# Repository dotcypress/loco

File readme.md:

# loco

Toy CNC platform.

## License

Licensed under either of

- Apache License, Version 2.0 ([LICENSE-APACHE](LICENSE-APACHE) or
  http://www.apache.org/licenses/LICENSE-2.0)
- MIT license ([LICENSE-MIT](LICENSE-MIT) or http://opensource.org/licenses/MIT)

at your option.

### Contribution

Unless you explicitly state otherwise, any contribution intentionally submitted
for inclusion in the work by you, as defined in the Apache-2.0 license, shall be
dual licensed as above, without any additional terms or conditions.

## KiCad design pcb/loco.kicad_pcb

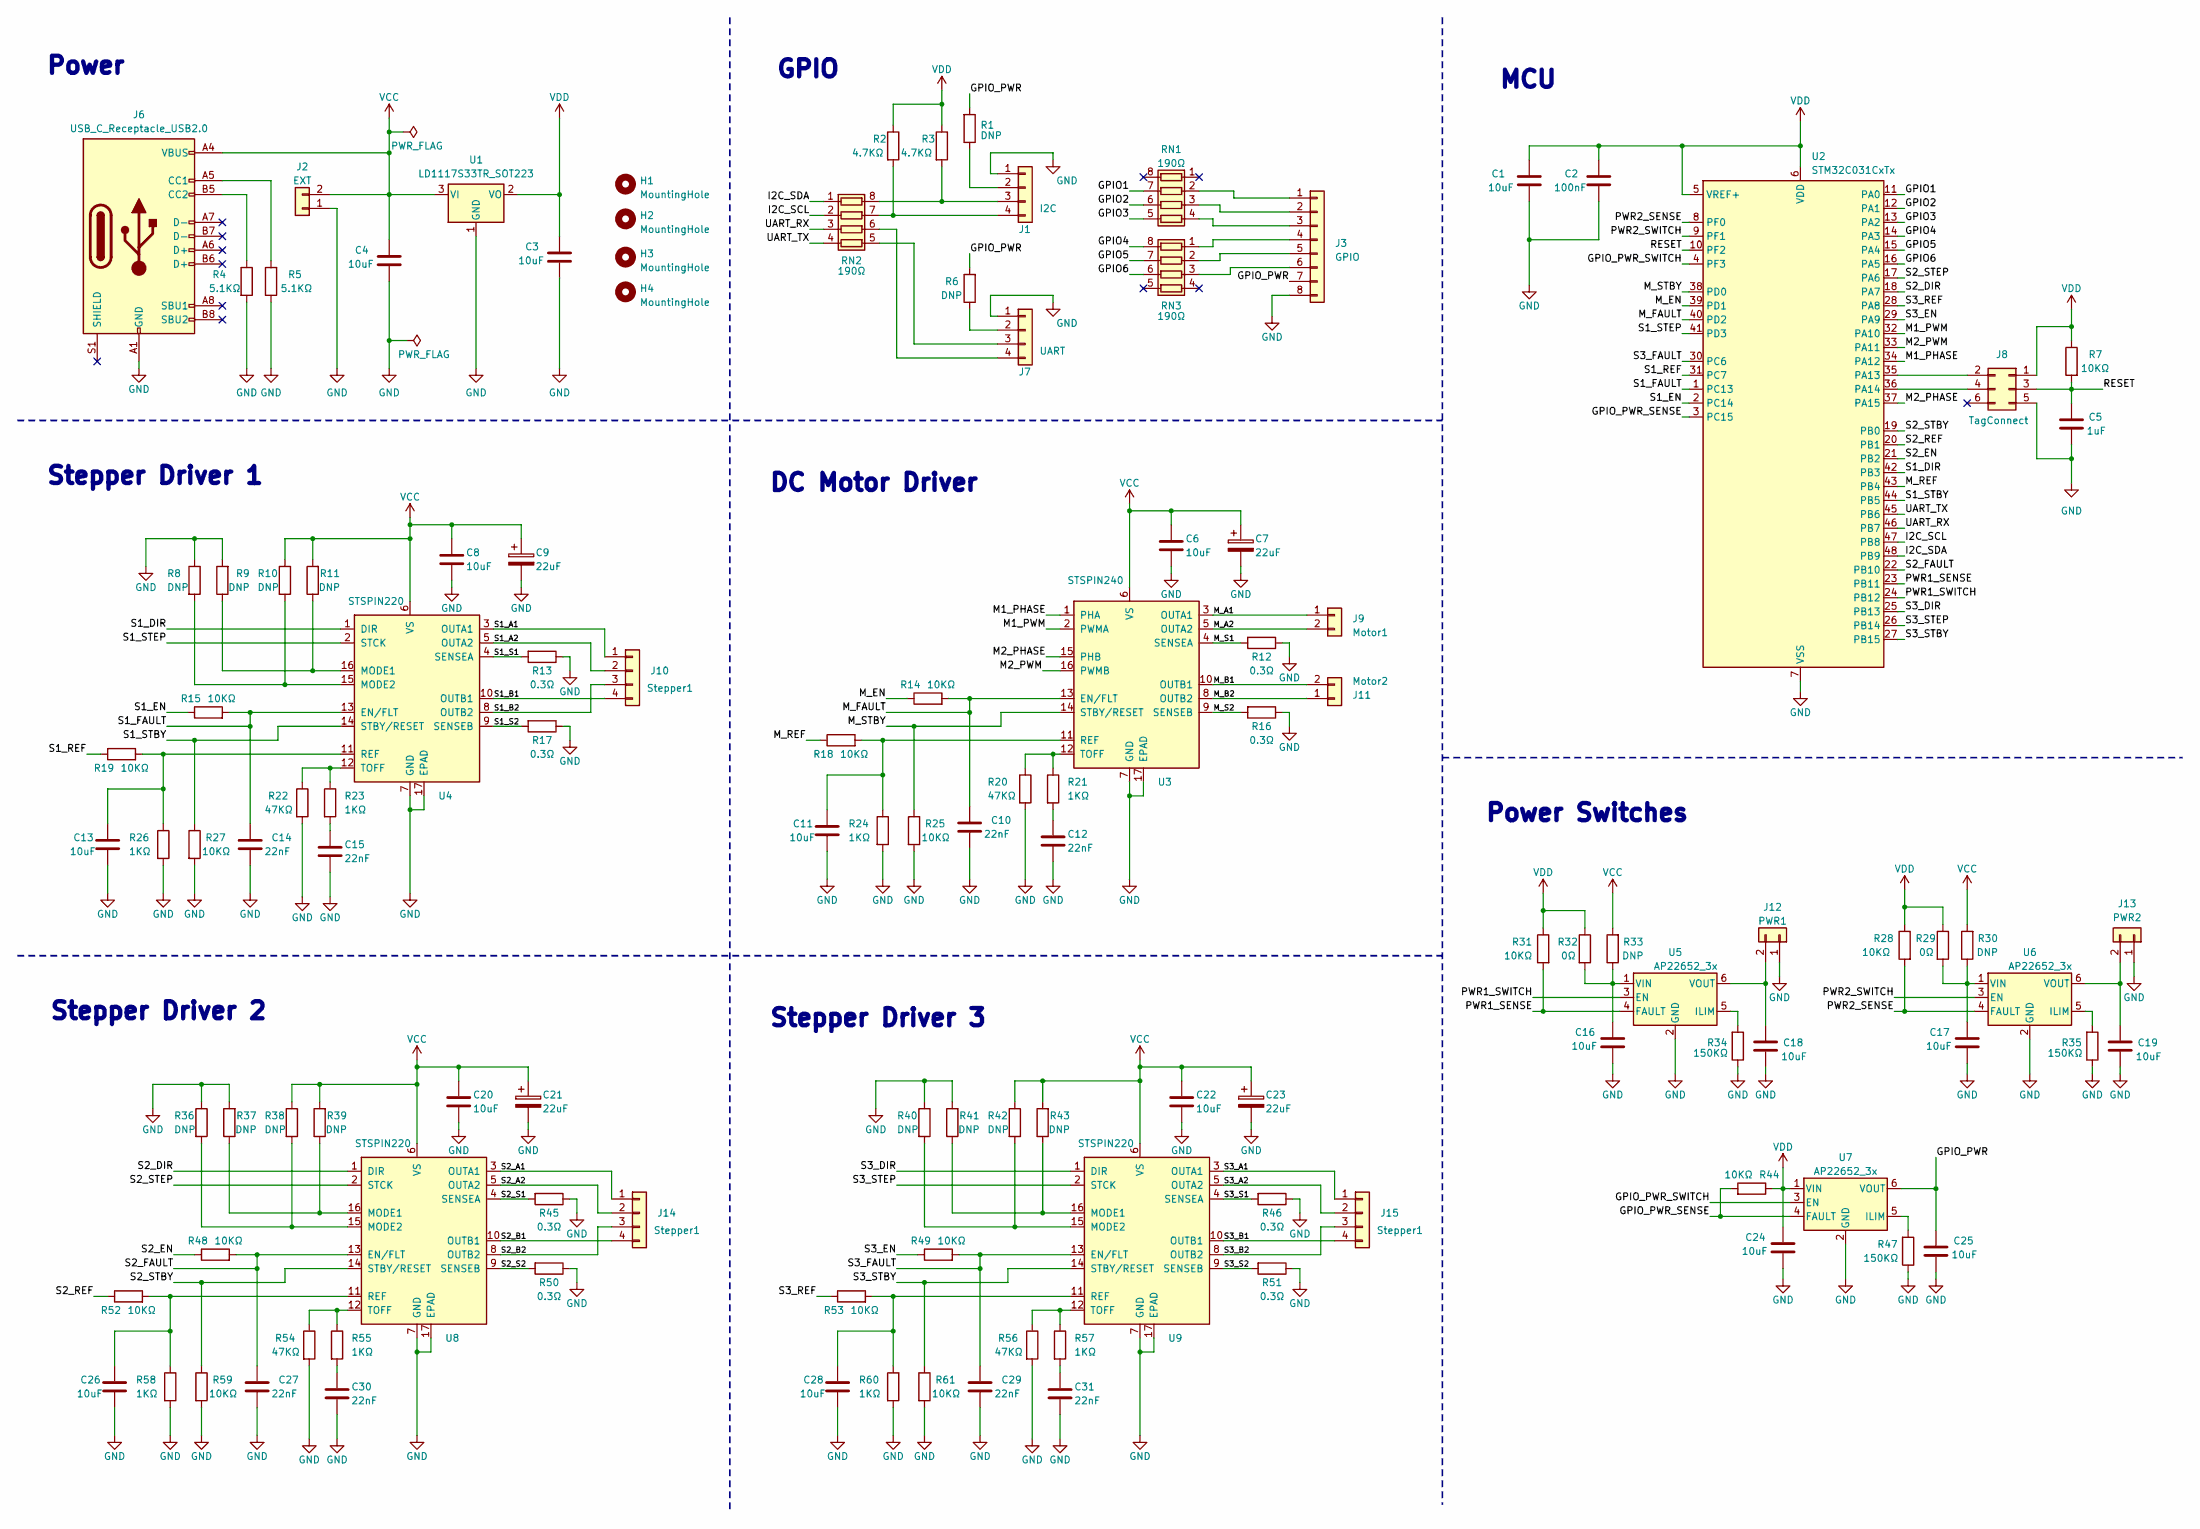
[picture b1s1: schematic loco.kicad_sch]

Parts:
C1, C3, C4, C6, C8, C11, C13, C16, C17, C18, C19, C20, C22, C24, C25, C26, C28: 10uF; C_0603_1608Metric
C2: 100nF; C_0603_1608Metric
C5: 1uF; C_0603_1608Metric
C7, C9, C21, C23: 22uF; CP_Elec_4x4.5
C10, C12, C14, C15, C27, C29, C30, C31: 22nF; C_0603_1608Metric
H1, H2, H3, H4: MountingHole; MountingHole_3.2mm_M3_Pad_Via
J1: I2C; JST_SH_BM04B-SRSS-TB_1x04-1MP_P1.00mm_Vertical
J2: EXT; JST_PH_B2B-PH-K_1x02_P2.00mm_Vertical
J3: GPIO; Header_03x06_P2.54mm_Vertical
J6: USB_C_Receptacle_USB2.0; USB_C_Receptacle_JAE_DX07S016JA3R1500
J7: UART; JST_SH_BM04B-SRSS-TB_1x04-1MP_P1.00mm_Vertical
J8: TagConnect; Tag-Connect_TC2030-IDC-NL_2x03_P1.27mm_Vertical
J9: Motor1; JST_PH_B2B-PH-K_1x02_P2.00mm_Vertical
J10, J14, J15: Stepper1; JST_PH_B4B-PH-K_1x04_P2.00mm_Vertical
J11: Motor2; JST_PH_B2B-PH-K_1x02_P2.00mm_Vertical
J12: PWR1; JST_PH_B2B-PH-K_1x02_P2.00mm_Vertical
J13: PWR2; JST_PH_B2B-PH-K_1x02_P2.00mm_Vertical
R1, R6, R8, R9, R10, R11, R30, R33, R36, R37, R38, R39, R40, R41, R42, R43: DNP; R_0603_1608Metric
R2, R3: 4.7KΩ; R_0603_1608Metric
R4, R5: 5.1KΩ; R_0603_1608Metric
R7, R14, R15, R18, R19, R25, R27, R28, R31, R44, R48, R49, R52, R53, R59, R61: 10KΩ; R_0603_1608Metric
R12, R13, R16, R17, R45, R46, R50, R51: 0.3Ω; R_1206_3216Metric
R20, R22, R54, R56: 47KΩ; R_0603_1608Metric
R21, R23, R24, R26, R55, R57, R58, R60: 1KΩ; R_0603_1608Metric
R29, R32: 0Ω; R_0603_1608Metric
R34, R35, R47: 150KΩ; R_0603_1608Metric
RN1, RN2, RN3: 190Ω; R_Array_Convex_4x0603
U1: LD1117S33TR_SOT223; SOT-223-3_TabPin2
U2: STM32C031CxTx; LQFP-48_7x7mm_P0.5mm
U3: STSPIN240; VQFN-16-1EP_3x3mm_P0.5mm_EP1.8x1.8mm
U4, U8, U9: STSPIN220; VQFN-16-1EP_3x3mm_P0.5mm_EP1.8x1.8mm
U5, U6, U7: AP22652_3x; SOT-23-6

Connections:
/GPIO1: RN1.7 (R2.2), U2.11 (PA0)
/GPIO2: RN1.6 (R3.2), U2.12 (PA1)
/GPIO3: RN1.5 (R4.2), U2.13 (PA2)
/GPIO4: RN3.8 (R1.2), U2.14 (PA3)
/GPIO5: RN3.7 (R2.2), U2.15 (PA4)
/GPIO6: RN3.6 (R3.2), U2.16 (PA5)
/GPIO_PWR: C25.1, J3.7, R1.2, R6.2, U7.6 (VOUT)
/GPIO_PWR_SENSE: R44.2, U2.3 (PC15), U7.4 (FAULT)
/GPIO_PWR_SWITCH: U2.4 (PF3), U7.3 (EN)
/I2C_SCL: RN2.2 (R2.1), U2.47 (PB8)
/I2C_SDA: RN2.1 (R1.1), U2.48 (PB9)
/M1_PHASE: U2.34 (PA12), U3.1 (PHA)
/M1_PWM: U2.32 (PA10), U3.2 (PWMA)
/M2_PHASE: U2.37 (PA15), U3.15 (PHB)
/M2_PWM: U2.33 (PA11), U3.16 (PWMB)
/M_A1: J9.1, U3.3 (OUTA1)
/M_A2: J9.2, U3.5 (OUTA2)
/M_B1: J11.2, U3.10 (OUTB1)
/M_B2: J11.1, U3.8 (OUTB2)
/M_EN: R14.1, U2.39 (PD1)
/M_FAULT: C10.1, R14.2, U2.40 (PD2), U3.13 (EN/FLT)
/M_REF: R18.1, U2.43 (PB4)
/M_S1: R12.2, U3.4 (SENSEA)
/M_S2: R16.2, U3.9 (SENSEB)
/M_STBY: R25.1, U2.38 (PD0), U3.14 (STBY/RESET)
/PWR1_SENSE: R31.2, U2.23 (PB11), U5.4 (FAULT)
/PWR1_SWITCH: U2.24 (PB12), U5.3 (EN)
/PWR2_SENSE: R28.2, U2.8 (PF0), U6.4 (FAULT)
/PWR2_SWITCH: U2.9 (PF1), U6.3 (EN)
/RESET: C5.1, J8.3, R7.2, U2.10 (PF2)
/S1_A1: J10.1, U4.3 (OUTA1)
/S1_A2: J10.2, U4.5 (OUTA2)
/S1_B1: J10.4, U4.10 (OUTB1)
/S1_B2: J10.3, U4.8 (OUTB2)
/S1_DIR: U2.42 (PB3), U4.1 (DIR)
/S1_EN: R15.1, U2.2 (PC14)
/S1_FAULT: C14.1, R15.2, U2.1 (PC13), U4.13 (EN/FLT)
/S1_REF: R19.1, U2.31 (PC7)
/S1_S1: R13.2, U4.4 (SENSEA)
/S1_S2: R17.2, U4.9 (SENSEB)
/S1_STBY: R27.1, U2.44 (PB5), U4.14 (STBY/RESET)
/S1_STEP: U2.41 (PD3), U4.2 (STCK)
/S2_A1: J14.1, U8.3 (OUTA1)
/S2_A2: J14.2, U8.5 (OUTA2)
/S2_B1: J14.4, U8.10 (OUTB1)
/S2_B2: J14.3, U8.8 (OUTB2)
/S2_DIR: U2.18 (PA7), U8.1 (DIR)
/S2_EN: R48.1, U2.21 (PB2)
/S2_FAULT: C27.1, R48.2, U2.22 (PB10), U8.13 (EN/FLT)
/S2_REF: R52.1, U2.20 (PB1)
/S2_S1: R45.2, U8.4 (SENSEA)
/S2_S2: R50.2, U8.9 (SENSEB)
/S2_STBY: R59.1, U2.19 (PB0), U8.14 (STBY/RESET)
/S2_STEP: U2.17 (PA6), U8.2 (STCK)
/S3_A1: J15.1, U9.3 (OUTA1)
/S3_A2: J15.2, U9.5 (OUTA2)
/S3_B1: J15.4, U9.10 (OUTB1)
/S3_B2: J15.3, U9.8 (OUTB2)
/S3_DIR: U2.25 (PB13), U9.1 (DIR)
/S3_EN: R49.1, U2.29 (PA9)
/S3_FAULT: C29.1, R49.2, U2.30 (PC6), U9.13 (EN/FLT)
/S3_REF: R53.1, U2.28 (PA8)
/S3_S1: R46.2, U9.4 (SENSEA)
/S3_S2: R51.2, U9.9 (SENSEB)
/S3_STBY: R61.1, U2.27 (PB15), U9.14 (STBY/RESET)
/S3_STEP: U2.26 (PB14), U9.2 (STCK)
/UART_RX: RN2.3 (R3.1), U2.46 (PB7)
/UART_TX: RN2.4 (R4.1), U2.45 (PB6)
GND: C1.2, C2.2, C3.2, C4.2, C5.2, C6.2, C7.2, C8.2, C9.2, C10.2, C11.2, C12.2, C13.2, C14.2, C15.2, C16.2, C17.2, C18.2, C19.2, C20.2, C21.2, C22.2, C23.2, C24.2, C25.2, C26.2, C27.2, C28.2, C29.2, C30.2, C31.2, J1.1, J2.1, J3.8, J6.A1 (GND), J7.1, J8.5, J12.1, J13.1, R4.2, R5.1, R8.1, R9.2, R12.1, R13.1, R16.1, R17.1, R20.2, R22.2, R24.2, R25.2, R26.2, R27.2, R34.1, R35.1, R36.1, R37.2, R40.1, R41.2, R45.1, R46.1, R47.1, R50.1, R51.1, R54.2, R56.2, R58.2, R59.2, R60.2, R61.2, U1.1 (GND), U2.7 (VSS), U3.7 (GND), U3.17 (EPAD), U4.7 (GND), U4.17 (EPAD), U5.2 (GND), U6.2 (GND), U7.2 (GND), U8.7 (GND), U8.17 (EPAD), U9.7 (GND), U9.17 (EPAD)
unnamed: C12.1, R21.2
unnamed: C15.1, R23.2
unnamed: C30.1, R55.2
unnamed: C31.1, R57.2
unnamed: J1.2, R1.1
unnamed: J1.3, R3.2, RN2.8 (R1.2)
unnamed: J1.4, R2.2, RN2.7 (R2.2)
unnamed: J3.1, RN1.2 (R2.1)
unnamed: J3.2, RN1.3 (R3.1)
unnamed: J3.3, RN1.4 (R4.1)
unnamed: J3.4, RN3.1 (R1.1)
unnamed: J3.5, RN3.2 (R2.1)
unnamed: J3.6, RN3.3 (R3.1)
unnamed: J6.A5 (CC1), R5.2
unnamed: J6.B5 (CC2), R4.1
unnamed: J7.2, R6.1
unnamed: J7.3, RN2.5 (R4.2)
unnamed: J7.4, RN2.6 (R3.2)
unnamed: J8.2, U2.35 (PA13)
unnamed: J8.4, U2.36 (PA14)
unnamed: C18.1, J12.2, U5.6 (VOUT)
unnamed: C19.1, J13.2, U6.6 (VOUT)
unnamed: C11.1, R18.2, R24.1, U3.11 (REF)
unnamed: R20.1, R21.1, U3.12 (TOFF)
unnamed: R9.1, R11.1, U4.16 (MODE1)
unnamed: R8.2, R10.2, U4.15 (MODE2)
unnamed: C13.1, R19.2, R26.1, U4.11 (REF)
unnamed: R22.1, R23.1, U4.12 (TOFF)
unnamed: R34.2, U5.5 (ILIM)
unnamed: C16.1, R32.2, R33.1, U5.1 (VIN)
unnamed: R35.2, U6.5 (ILIM)
unnamed: C17.1, R29.2, R30.1, U6.1 (VIN)
unnamed: R47.2, U7.5 (ILIM)
unnamed: R37.1, R39.1, U8.16 (MODE1)
unnamed: R36.2, R38.2, U8.15 (MODE2)
unnamed: C26.1, R52.2, R58.1, U8.11 (REF)
unnamed: R54.1, R55.1, U8.12 (TOFF)
unnamed: R41.1, R43.1, U9.16 (MODE1)
unnamed: R40.2, R42.2, U9.15 (MODE2)
unnamed: C28.1, R53.2, R60.1, U9.11 (REF)
unnamed: R56.1, R57.1, U9.12 (TOFF)
VCC: C4.1, C6.1, C7.1, C8.1, C9.1, C20.1, C21.1, C22.1, C23.1, J2.2, J6.A4 (VBUS), J6.A9 (VBUS), R10.1, R11.2, R30.2, R33.2, R38.1, R39.2, R42.1, R43.2, U1.3 (VI), U3.6 (VS), U4.6 (VS), U8.6 (VS), U9.6 (VS)
VDD: C1.1, C2.1, C3.1, C24.1, J8.1, R2.1, R3.1, R7.1, R28.1, R29.1, R31.1, R32.1, R44.1, U1.2 (VO), U2.5 (VREF+), U2.6 (VDD), U7.1 (VIN)

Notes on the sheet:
GPIO
Stepper Driver 3
Power Switches
Stepper Driver 1
DC Motor Driver
MCU
Power
Stepper Driver 2

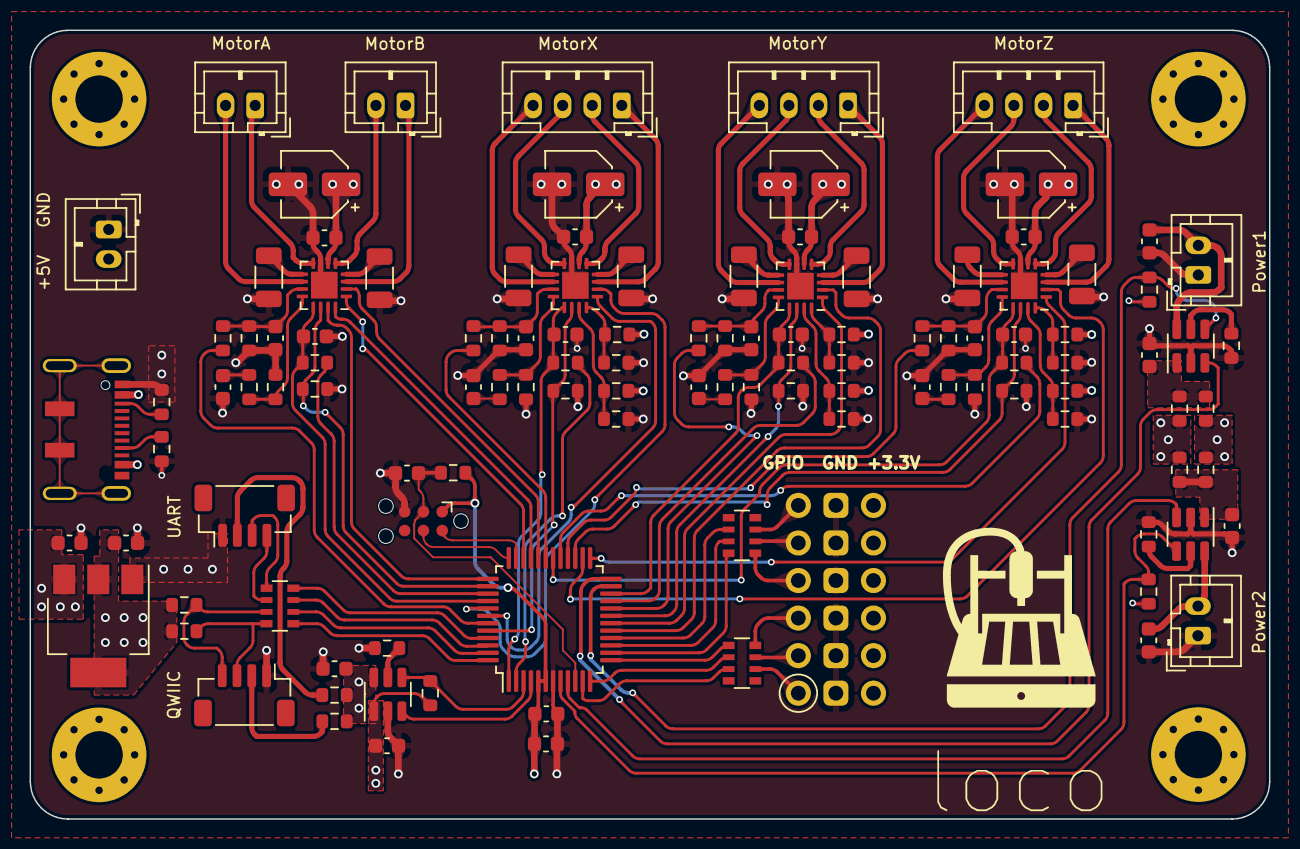
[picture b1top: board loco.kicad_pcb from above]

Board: 4 copper layers, 83.8 x 53.3 mm, 121 parts (0 on the bottom side), 112 nets.

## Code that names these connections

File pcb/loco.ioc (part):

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Mcu.Name=STM32C031C(4-6)Ux
Mcu.Package=UFQFPN48
Mcu.UserName=STM32C031C6Ux
PA0.GPIOParameters=GPIO_Label
PA0.GPIO_Label=GPIO1
PA0.Signal=S_TIM1_CH1
PA1.GPIOParameters=GPIO_Label
PA1.GPIO_Label=GPIO2
PA1.Signal=S_TIM1_CH2
PA10.GPIOParameters=GPIO_Label
PA10.GPIO_Label=M2_PWM
PA10.Signal=S_TIM1_CH3
PA11\ [PA9].GPIOParameters=GPIO_Label
PA11\ [PA9].GPIO_Label=M1_PWM
PA11\ [PA9].Signal=S_TIM1_CH4
PA12\ [PA10].GPIOParameters=GPIO_Label
PA12\ [PA10].GPIO_Label=M1_PHASE
PA12\ [PA10].Signal=GPIO_Output
PA13.Mode=Serial_Wire
PA13.Signal=DEBUG_SWDIO
PA14-BOOT0.Mode=Serial_Wire
PA14-BOOT0.Signal=DEBUG_SWCLK
PA15.GPIOParameters=GPIO_Label
PA15.GPIO_Label=M2_PHASE
PA15.Signal=GPIO_Input
PA2.GPIOParameters=GPIO_Label
PA2.GPIO_Label=GPIO3
PA2.Mode=IN2
PA2.Signal=ADC1_IN2
PA3.GPIOParameters=GPIO_Label
PA3.GPIO_Label=GPIO4
PA3.Mode=IN3
PA3.Signal=ADC1_IN3
PA4.GPIOParameters=GPIO_Label
PA4.GPIO_Label=GPIO5
PA4.Signal=GPIO_Output
PA5.GPIOParameters=GPIO_Label
PA5.GPIO_Label=GPIO6
PA5.Mode=IN5
PA5.Signal=ADC1_IN5
PA6.GPIOParameters=GPIO_Label
PA6.GPIO_Label=S2_STEP
PA6.Signal=GPIO_Output
PA7.GPIOParameters=GPIO_Label
PA7.GPIO_Label=S2_DIR
PA7.Signal=GPIO_Output
PA8.GPIOParameters=GPIO_Label
PA8.GPIO_Label=S3_REF
PA8.Signal=S_TIM3_CH3
PA9.GPIOParameters=GPIO_Label
PA9.GPIO_Label=S3_EN
PA9.Signal=GPIO_Output
PB0.GPIOParameters=GPIO_Label
PB0.GPIO_Label=S2_RST
PB0.Signal=GPIO_Output
PB1.GPIOParameters=GPIO_Label
PB1.GPIO_Label=S2_REF
PB1.Signal=S_TIM3_CH4
PB10.GPIOParameters=GPIO_Label
PB10.GPIO_Label=S2_FAULT
PB10.Signal=GPIO_Input
PB11.GPIOParameters=GPIO_Label
PB11.GPIO_Label=PWR2_SENSE
PB11.Signal=GPIO_Input
PB12.GPIOParameters=GPIO_Label
PB12.GPIO_Label=PWR2_SWITCH
PB12.Signal=GPIO_Output
PB13.GPIOParameters=GPIO_Label
PB13.GPIO_Label=S3_DIR
PB13.Signal=GPIO_Output
PB14.GPIOParameters=GPIO_Label
PB14.GPIO_Label=S3_STEP
PB14.Signal=GPIO_Output
PB15.GPIOParameters=GPIO_Label
PB15.GPIO_Label=S3_DIR
PB15.Signal=GPIO_Output
PB2.GPIOParameters=GPIO_Label
PB2.GPIO_Label=S2_EN
PB2.Signal=GPIO_Output
PB3.GPIOParameters=GPIO_Label
PB3.GPIO_Label=S1_DIR
PB3.Signal=GPIO_Output
PB4.GPIOParameters=GPIO_Label
PB4.GPIO_Label=S1_REF
PB4.Signal=S_TIM3_CH1
PB5.GPIOParameters=GPIO_Label
PB5.GPIO_Label=S1_RST
PB5.Signal=GPIO_Output
PB6.Mode=Asynchronous
PB6.Signal=USART1_TX
PB7.Mode=Asynchronous
PB7.Signal=USART1_RX
PB8.Mode=I2C
PB8.Signal=I2C1_SCL
PB9.Mode=I2C
PB9.Signal=I2C1_SDA
PC13.GPIOParameters=GPIO_Label
PC13.GPIO_Label=S1_EN
PC13.Signal=GPIO_Output
PC14-OSCX_IN\ (PC14).GPIOParameters=GPIO_Label
PC14-OSCX_IN\ (PC14).GPIO_Label=S1_FAULT
PC14-OSCX_IN\ (PC14).Signal=GPIO_Input
PC15-OSCX_OUT\ (PC15).GPIOParameters=GPIO_Label
PC15-OSCX_OUT\ (PC15).GPIO_Label=GPIO_PWR_SENSE
PC15-OSCX_OUT\ (PC15).Signal=GPIO_Output
PC6.GPIOParameters=GPIO_Label
PC6.GPIO_Label=S3_FAULT
PC6.Signal=GPIO_Input
PC7.GPIOParameters=GPIO_Label
PC7.GPIO_Label=M_REF
PC7.Signal=S_TIM3_CH2
PD0.GPIOParameters=GPIO_Label
PD0.GPIO_Label=M_RST
PD0.Signal=GPIO_Output
PD1.GPIOParameters=GPIO_Label
PD1.GPIO_Label=M_EN
PD1.Signal=GPIO_Output
PD2.GPIOParameters=GPIO_Label
PD2.GPIO_Label=M_FAULT
PD2.Signal=GPIO_Input
PD3.GPIOParameters=GPIO_Label
PD3.GPIO_Label=S1_STEP
PD3.Signal=GPIO_Output
PF0-OSC_IN\ (PF0).GPIOParameters=GPIO_Label
PF0-OSC_IN\ (PF0).GPIO_Label=RST
PF0-OSC_IN\ (PF0).Signal=GPXTI0
PF1-OSC_OUT\ (PF1).GPIOParameters=GPIO_Label
PF1-OSC_OUT\ (PF1).GPIO_Label=PWR1_SWITCH
PF1-OSC_OUT\ (PF1).Signal=GPIO_Output
PF2-NRST.GPIOParameters=GPIO_Label
PF2-NRST.GPIO_Label=PWR1_SENSE
PF2-NRST.Signal=GPIO_Input
PF3.GPIOParameters=GPIO_Label
PF3.GPIO_Label=GPIO_PWR_SWITCH
PF3.Signal=GPIO_Input
RCC.HSE_VALUE=8000000
RCC.SYSCLKFreq_VALUE=12000000
board=custom

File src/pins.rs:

use crate::hal::gpio::{gpioa::*, gpiob::*, gpioc::*, gpiod::*, gpiof::*};
use hal::gpio::{DefaultMode, Floating, Input, OpenDrain, Output, PushPull};
use hal::prelude::*;
use hal::rcc::Rcc;
use hal::stm32::*;

// SWD
pub type SwdIo = PA13<DefaultMode>;
pub type SwdClk = PA14<DefaultMode>;

/// I2C
pub type I2cScl = PB8<Output<OpenDrain>>;
pub type I2cSda = PB9<Output<OpenDrain>>;

/// UART
pub type UartTx = PB6<DefaultMode>;
pub type UartRx = PB7<DefaultMode>;

/// GPIO
pub type G1 = PA0<DefaultMode>;
pub type G2 = PA1<DefaultMode>;
pub type G3 = PA2<DefaultMode>;
pub type G4 = PA3<DefaultMode>;
pub type G5 = PA4<DefaultMode>;
pub type G6 = PA5<DefaultMode>;

// DC Motors
pub type MotorRef = PB4<DefaultMode>;
pub type MotorFault = PD2<Input<Floating>>;
pub type MotorStandby = PD0<Output<PushPull>>;
pub type MotorEnable = PD1<Output<PushPull>>;
pub type MotorAPhase = PA15<Output<PushPull>>;
pub type MotorAPWM = PA11<DefaultMode>;
pub type MotorBPhase = PA12<Output<PushPull>>;
pub type MotorBPWM = PA10<DefaultMode>;

// Stepper Motors
pub type MotorXRef = PC7<DefaultMode>;
pub type MotorXFault = PC13<Input<Floating>>;
pub type MotorXStandby = PB5<Output<PushPull>>;
pub type MotorXEnable = PC14<Output<PushPull>>;
pub type MotorXStep = PD3<Output<PushPull>>;
pub type MotorXDir = PB3<Output<PushPull>>;

pub type MotorYRef = PB1<DefaultMode>;
pub type MotorYFault = PB10<Input<Floating>>;
pub type MotorYStandby = PB0<Output<PushPull>>;
pub type MotorYEnable = PB2<Output<PushPull>>;
pub type MotorYStep = PA6<Output<PushPull>>;
pub type MotorYDir = PA7<Output<PushPull>>;

pub type MotorZRef = PA8<DefaultMode>;
pub type MotorZFault = PC6<Input<Floating>>;
pub type MotorZStandby = PB15<Output<PushPull>>;
pub type MotorZEnable = PA9<Output<PushPull>>;
pub type MotorZStep = PB14<Output<PushPull>>;
pub type MotorZDir = PB13<Output<PushPull>>;

// Power switches
pub type Switch1Enable = PB12<Output<PushPull>>;
pub type Switch1Sense = PB11<Input<Floating>>;

pub type Switch2Enable = PF1<Output<PushPull>>;
pub type Switch2Sense = PF0<Input<Floating>>;

pub type Switch3Enable = PF3<Output<PushPull>>;
pub type Switch3Sense = PC15<Input<Floating>>;

pub struct Gpio {
    pub g1: G1,
    pub g2: G2,
    pub g3: G3,
    pub g4: G4,
    pub g5: G5,
    pub g6: G6,
}

pub struct Pins {
    // I2C
    pub i2c_scl: I2cScl,
    pub i2c_sda: I2cSda,

    // SWD
    pub swd_io: SwdIo,
    pub swd_clk: SwdClk,

    // UART
    pub uart_tx: UartTx,
    pub uart_rx: UartRx,

    // GPIO
    pub gpio: Gpio,

    // DC Motors
    pub motor_ref: MotorRef,
    pub motor_fault: MotorFault,
    pub motor_standby: MotorStandby,
    pub motor_enable: MotorEnable,
    pub motor_a_phase: MotorAPhase,
    pub motor_a_pwm: MotorAPWM,
    pub motor_b_phase: MotorBPhase,
    pub motor_b_pwm: MotorBPWM,

    // Stepper Motors
    pub motor_x_ref: MotorXRef,
    pub motor_x_fault: MotorXFault,
    pub motor_x_standby: MotorXStandby,
    pub motor_x_enable: MotorXEnable,
    pub motor_x_step: MotorXStep,
    pub motor_x_dir: MotorXDir,

    pub motor_y_ref: MotorYRef,
    pub motor_y_fault: MotorYFault,
    pub motor_y_standby: MotorYStandby,
    pub motor_y_enable: MotorYEnable,
    pub motor_y_step: MotorYStep,
    pub motor_y_dir: MotorYDir,

    pub motor_z_ref: MotorZRef,
    pub motor_z_fault: MotorZFault,
    pub motor_z_standby: MotorZStandby,
    pub motor_z_enable: MotorZEnable,
    pub motor_z_step: MotorZStep,
    pub motor_z_dir: MotorZDir,

    // Power switches
    pub switch1_enable: Switch1Enable,
    pub switch1_sense: Switch1Sense,

    pub switch2_enable: Switch2Enable,
    pub switch2_sense: Switch2Sense,

    pub switch3_enable: Switch3Enable,
    pub switch3_sense: Switch3Sense,
}

impl Pins {
    pub fn new(
        gpioa: GPIOA,
        gpiob: GPIOB,
        gpioc: GPIOC,
        gpiod: GPIOD,
        gpiof: GPIOF,
        rcc: &mut Rcc,
    ) -> Self {
        let port_a = gpioa.split(rcc);
        let port_b = gpiob.split(rcc);
        let port_c = gpioc.split(rcc);
        let port_d = gpiod.split(rcc);
        let port_f = gpiof.split(rcc);

        Self {
            // I2C
            i2c_scl: port_b.pb8.into_open_drain_output_in_state(PinState::High),
            i2c_sda: port_b.pb9.into_open_drain_output_in_state(PinState::High),

            // SWD
            swd_io: port_a.pa13,
            swd_clk: port_a.pa14,

            // UART
            uart_tx: port_b.pb6,
            uart_rx: port_b.pb7,

            // GPIO
            gpio: Gpio {
                g1: port_a.pa0,
                g2: port_a.pa1,
                g3: port_a.pa2,
                g4: port_a.pa3,
                g5: port_a.pa4,
                g6: port_a.pa5,
            },

            // DC Motors
            motor_ref: port_b.pb4,
            motor_fault: port_d.pd2.into(),
            motor_standby: port_d.pd0.into(),
            motor_enable: port_d.pd1.into(),
            motor_a_phase: port_a.pa15.into(),
            motor_b_phase: port_a.pa12.into(),
            motor_a_pwm: port_a.pa11,
            motor_b_pwm: port_a.pa10,

            // Stepper Motors
            motor_x_ref: port_c.pc7,
            motor_x_fault: port_c.pc13.into(),
            motor_x_standby: port_b.pb5.into(),
            motor_x_enable: port_c.pc14.into(),
            motor_x_step: port_d.pd3.into(),
            motor_x_dir: port_b.pb3.into(),

            motor_y_ref: port_b.pb1,
            motor_y_fault: port_b.pb10.into(),
            motor_y_standby: port_b.pb0.into(),
            motor_y_enable: port_b.pb2.into(),
            motor_y_step: port_a.pa6.into(),
            motor_y_dir: port_a.pa7.into(),

            motor_z_ref: port_a.pa8,
            motor_z_fault: port_c.pc6.into(),
            motor_z_standby: port_b.pb15.into(),
            motor_z_enable: port_a.pa9.into(),
            motor_z_step: port_b.pb14.into(),
            motor_z_dir: port_b.pb13.into(),

            // Power switches
            switch1_enable: port_b.pb12.into(),
            switch1_sense: port_b.pb11.into(),

            switch2_enable: port_f.pf1.into(),
            switch2_sense: port_f.pf0.into(),

            switch3_enable: port_f.pf3.into(),
            switch3_sense: port_c.pc15.into(),
        }
    }
}

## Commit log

2022-07-21 update schematics
2022-07-25 add flash store
2022-07-25 bump version
2022-07-25 add build.rs
2022-07-28 add BOM
2022-07-29 pcb rev 0.2
2022-07-30 update motor pins
2022-07-31 add stepper driver
2022-07-31 oops
2022-07-31 steppert reverse
2022-07-31 refactoring
2022-08-07 pcb rev 2
2022-08-08 update kvs version
2022-08-29 fix pull-down for spi flash
2022-08-30 flash store
2022-08-30 update manifest
2023-01-20 editor config
2023-02-05 pcb rev.0x03
2023-02-09 update pins
2023-02-16 stepper motor control
2023-02-17 add dc motor driver
2023-02-19 rev 0x04
2023-02-20 add photo
2023-02-20 update motor controller
